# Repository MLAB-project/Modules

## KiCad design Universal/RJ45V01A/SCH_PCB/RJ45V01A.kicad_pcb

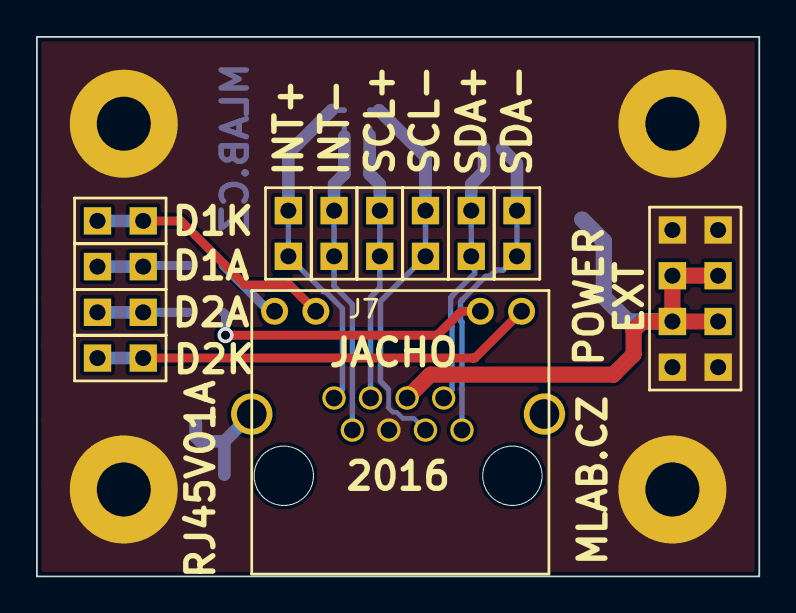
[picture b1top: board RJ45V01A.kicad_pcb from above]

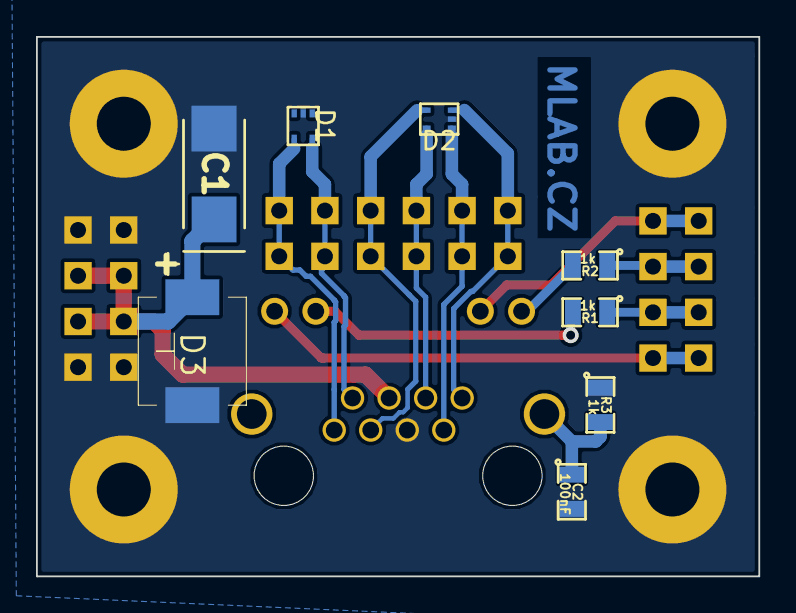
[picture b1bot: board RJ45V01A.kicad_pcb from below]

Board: 2 copper layers, 40.1 x 30.0 mm, 24 parts (8 on the bottom side), 15 nets.

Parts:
C1: 47uF; TantalC_SizeC_Reflow
C2: 100nF; SMD-0805
D1, D2: SP1001-04XTG; SOT-553
D3: SM15T18A; Diode-SMC_Standard
J1: JUMP_4X2; Straight_2x04
J3: JUMP_2x1; Straight_1x02
J4, J5, J6, J8, J9, J10, J11, J12, J13: JUMP_2x1; Straight_2x01
J7: RJ45_RJHSE-5384; RJHSE-5384(RJ45)
M1, M2, M3, M4: HOLE; MountingHole_3mm
R1, R2, R3: 1k; SMD-0805

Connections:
/D1_A: J6.1, J6.2, R2.1
/D1_K: J3.1, J3.2, J7.11
/D2_A: J5.1, J5.2, R1.1
/D2_K: J4.1, J4.2, J7.9
/INT+: D2.3, J7.8, J8.1, J8.2
/INT-: D2.1, J7.7, J9.1, J9.2
/SCL+: D2.5, J7.6, J10.1, J10.2
/SCL-: D2.4, J7.3, J11.1, J11.2
/SDA+: D1.5, J7.2, J12.1, J12.2
/SDA-: D1.4, J7.1, J13.1, J13.2
GND: C1.2, C2.2, D1.2, D2.2, D3.1, J1.1, J1.2, J1.7, J1.8, J7.5, M1.1, M2.1, M3.1, M4.1, R3.1
unnamed: C2.1, J7.13, R3.2
unnamed: J7.10, R1.2
unnamed: J7.12, R2.2
VCC: C1.1, D3.2, J1.3, J1.4, J1.5, J1.6, J7.4

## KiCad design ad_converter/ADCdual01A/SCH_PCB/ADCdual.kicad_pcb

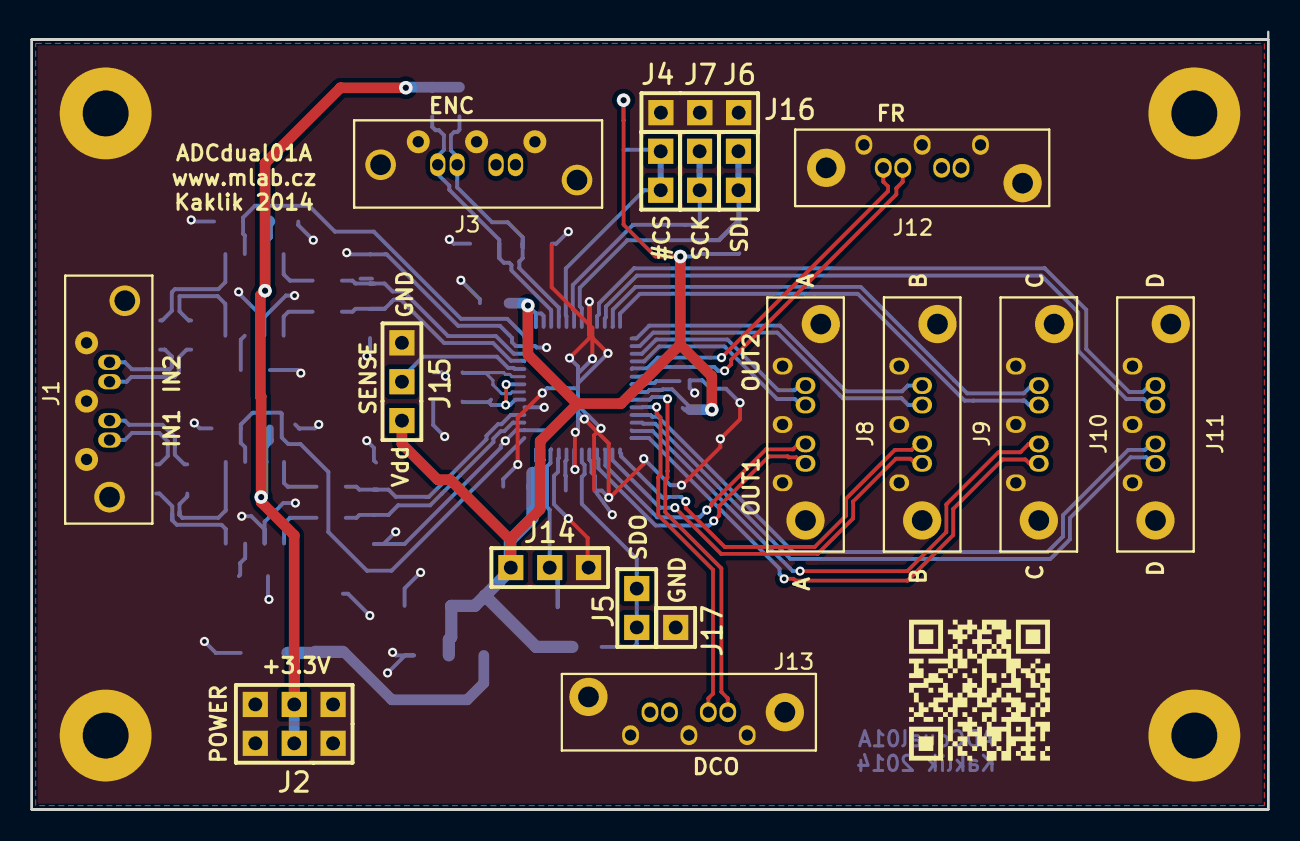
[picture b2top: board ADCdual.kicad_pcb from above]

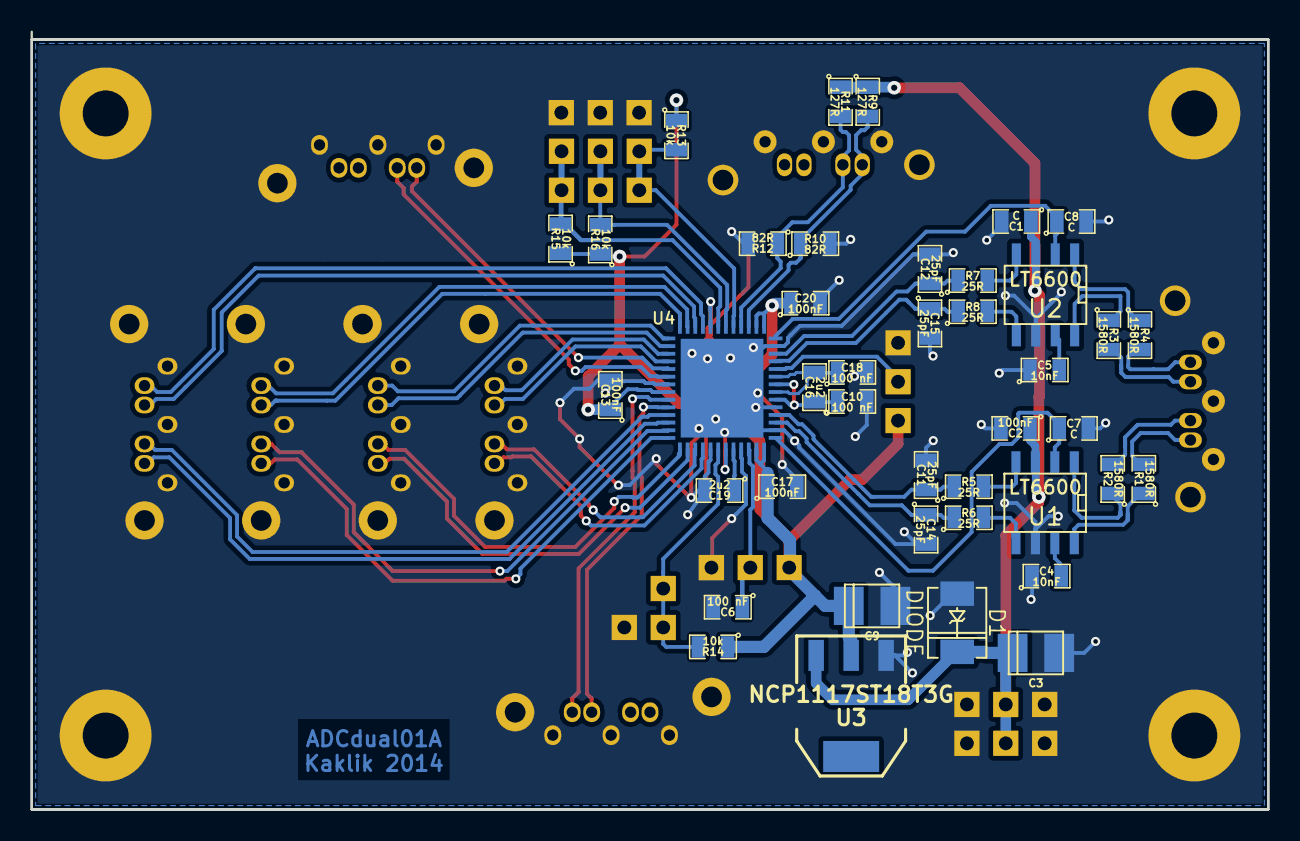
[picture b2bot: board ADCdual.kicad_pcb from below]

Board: 2 copper layers, 80.8 x 50.8 mm, 62 parts (41 on the bottom side), 54 nets.

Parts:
C1, C7, C8: C; SM0805
C2, C13, C17, C20: 100nF; SM0805
C3, C9: 10uF; c_tant_B
C4, C5: 10nF; SM0805
C6, C10, C18: 100 nF; SM0805
C11, C12, C14, C15: 25pF; SM0805
C16, C19: 2u2; SM0805
D1: DIODE; DO-214AC(SMA)
J1, J3: SATA7-67491-1030; SATA-7_THT_VERT
J2: JUMP_3X2_CONN; Pin_Header_Straight_2x03
J4, J5, J6, J7: JUMP_2_CONN; Pin_Header_Straight_2x01
J8, J9, J10, J11, J12, J13: SATA7-67491-1030; SATA-7_THT_VERT_2
J14: SENSE; Pin_Header_Straight_1x03
J15: PAR/SER; Pin_Header_Straight_1x03
J16: CONN_3; Pin_Header_Straight_1x03
J17: CONN_1; Pin_Header_Straight_1x01
P1, P2, P3, P4: CONN_1; MountingHole_3mm
R1, R2, R3, R4: 1580R; SM0805
R5, R6, R7, R8: 25R; SM0805
R9, R11: 127R; SM0805
R10, R12: 82R; SM0805
R13, R14, R15, R16: 10k; SM0805
U1, U2: LT6600; SO8E
U3: NCP1117ST18T3G; SOT223
U4: LTC2271; QFN52+1EP_HandSoldering

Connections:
3V3: C1.1, C2.1, C3.1, D1.2, J2.2, J2.5, R9.1, R11.1, U1.3, U2.3, U3.3
+1.8V: C9.1, C13.1, C17.1, C20.1, J14.1, J15.1, R13.1, R14.1, R15.1, R16.1, U3.2, U4.15, U4.16, U4.34, U4.51, U4.52
DGND: C1.2, C2.2, C3.2, C4.1, C5.1, C6.2, C7.2, C8.2, C9.2, C10.2, C11.2, C12.2, C13.2, C14.2, C15.2, C17.2, C18.2, C19.2, C20.2, D1.1, J1.1, J1.4, J1.7, J1.8, J1.9, J2.1, J2.3, J2.4, J2.6, J3.1, J3.4, J3.7, J3.8, J3.9, J8.1, J8.4, J8.7, J8.8, J8.9, J9.1, J9.4, J9.7, J9.8, J9.9, J10.1, J10.4, J10.7, J10.8, J10.9, J11.1, J11.4, J11.7, J11.8, J11.9, J12.1, J12.4, J12.7, J12.8, J12.9, J13.1, J13.4, J13.7, J13.8, J13.9, J14.3, J15.3, J16.1, J16.2, J16.3, J17.1, P1.1, P2.1, P3.1, P4.1, R10.2, R12.2, U1.6, U2.6, U3.1, U4.2, U4.5, U4.13, U4.22, U4.33, U4.45, U4.47, U4.49, U4.53
unnamed: C4.2, U1.7
unnamed: C5.2, U2.7
unnamed: C6.1, J14.2, U4.50
unnamed: C7.1, U1.2, U4.1
unnamed: C8.1, U2.2, U4.14
unnamed: C10.1, C16.1, U4.6, U4.8
unnamed: C11.1, R5.1, U4.4
unnamed: C12.1, R7.1, U4.12
unnamed: C14.1, R6.1, U4.3
unnamed: C15.1, R8.1, U4.11
unnamed: C16.2, C18.1, U4.7, U4.9
unnamed: C19.1, U4.48
unnamed: J1.2, R1.2
unnamed: J1.3, R2.2
unnamed: J1.5, R3.2
unnamed: J1.6, R4.2
unnamed: J3.2, R9.2, R10.1, U4.17
unnamed: J3.3, R11.2, R12.1, U4.18
unnamed: J4.1, J4.2, R13.2, U4.19
unnamed: J5.1, J5.2, R14.2, U4.46
unnamed: J6.1, J6.2, R15.2, U4.21
unnamed: J7.1, J7.2, R16.2, U4.20
unnamed: J8.2, U4.44
unnamed: J8.3, U4.43
unnamed: J8.5, U4.30
unnamed: J8.6, U4.29
unnamed: J9.2, U4.42
unnamed: J9.3, U4.41
unnamed: J9.5, U4.28
unnamed: J9.6, U4.27
unnamed: J10.2, U4.40
unnamed: J10.3, U4.39
unnamed: J10.5, U4.26
unnamed: J10.6, U4.25
unnamed: J11.2, U4.38
unnamed: J11.3, U4.37
unnamed: J11.5, U4.24
unnamed: J11.6, U4.23
unnamed: J12.2, U4.31
unnamed: J12.3, U4.32
unnamed: J13.2, U4.35
unnamed: J13.3, U4.36
unnamed: J15.2, U4.10
unnamed: R1.1, U1.8
unnamed: R2.1, U1.1
unnamed: R3.1, U2.8
unnamed: R4.1, U2.1
unnamed: R5.2, U1.4
unnamed: R6.2, U1.5
unnamed: R7.2, U2.4
unnamed: R8.2, U2.5

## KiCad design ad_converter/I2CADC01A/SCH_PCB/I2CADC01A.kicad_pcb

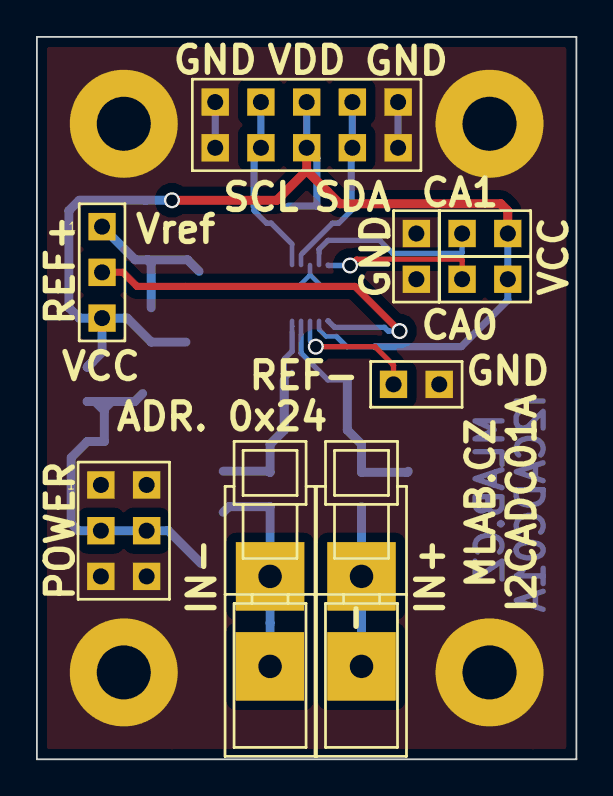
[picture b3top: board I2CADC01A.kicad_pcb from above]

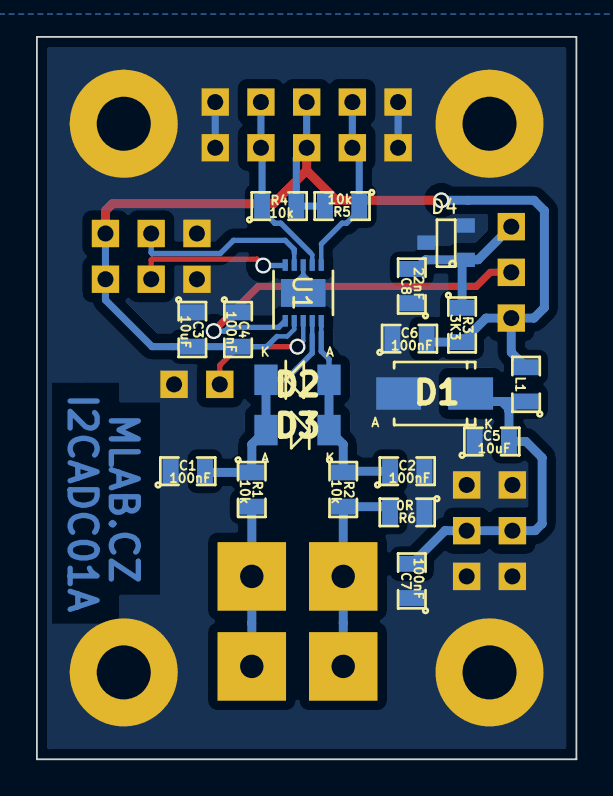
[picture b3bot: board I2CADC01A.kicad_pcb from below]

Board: 2 copper layers, 30.0 x 40.1 mm, 33 parts (20 on the bottom side), 14 nets.

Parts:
C1, C2, C4, C6, C7: 100nF; SMD-0805
C3, C5: 10uF; SMD-0805
C8: 22nF; SMD-0805
D1: M4; SMA_Standard
D2, D3: BAT46; MiniMELF_Standard
D4: LM4041-adj; SOT-23
J1: JUMP_3X2; Straight_2x03
J3, J8: CONN_2; Straight_2x01
J4: CONN_3; Straight_1x03
J5, J6: JUMP2_2x1; Straight_2x01
J7: JUMP_5X2; Straight_2x05
L1: BLM21PG300SN1D; SMD-0805
M1, M2, M3, M4: HOLE; MountingHole_3mm
P1, P2: _; WAGO256
R1, R2, R4, R5: 10k; SMD-0805
R3: 3K3; SMD-0805
R6: 0R; SMD-0805
U1: LTC2485; DFN-10-1EP_3x3mm_Pitch0.5mm

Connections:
/CA0: J5.2, U1.10
/CA1: J6.2, U1.9
/SCL: J7.7, J7.8, R5.1, U1.6
/SDA: J7.3, J7.4, R4.1, U1.7
GND: C1.1, C2.2, C3.1, C4.1, C5.1, C6.1, C7.1, C8.1, D1.1, D4.2, D4.3, J1.1, J1.2, J1.5, J1.6, J3.1, J7.1, J7.2, J7.9, J7.10, J8.1, J8.2, M1.1, M2.1, M3.1, M4.1, R6.1, U1.8, U1.11
unnamed: C1.2, D2.1, D3.2, R1.1, U1.4
unnamed: C2.1, D2.2, D3.1, R2.1, U1.5
unnamed: C5.2, C7.2, D1.2, J1.3, J1.4, L1.1
unnamed: C8.2, D4.1, J4.1, R3.1
unnamed: J3.2, U1.3
unnamed: J4.2, U1.1
unnamed: P1.1, R1.2
unnamed: P2.1, R2.2, R6.2
VCC: C3.2, C4.2, C6.2, J4.3, J5.1, J6.1, J7.5, J7.6, L1.2, R3.2, R4.2, R5.2, U1.2

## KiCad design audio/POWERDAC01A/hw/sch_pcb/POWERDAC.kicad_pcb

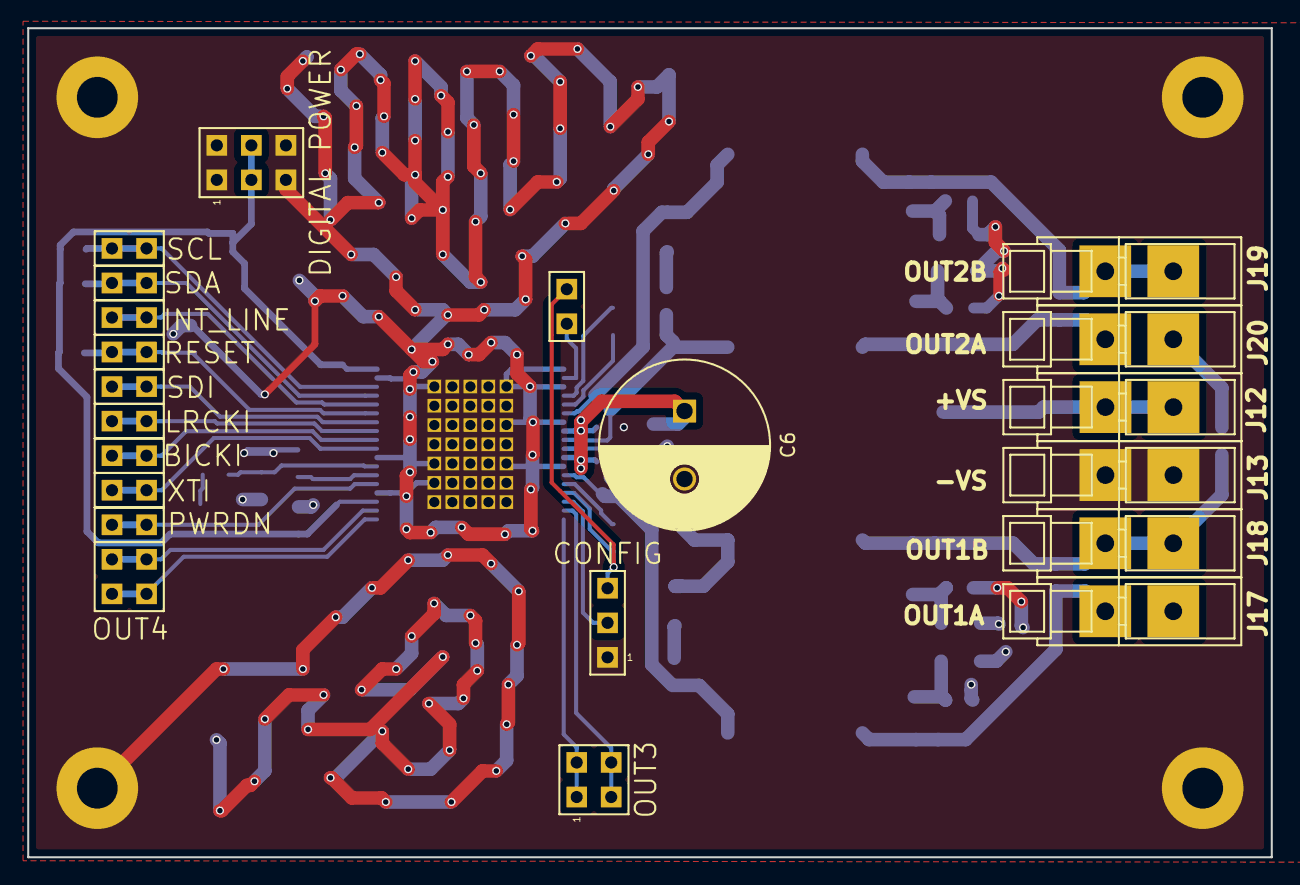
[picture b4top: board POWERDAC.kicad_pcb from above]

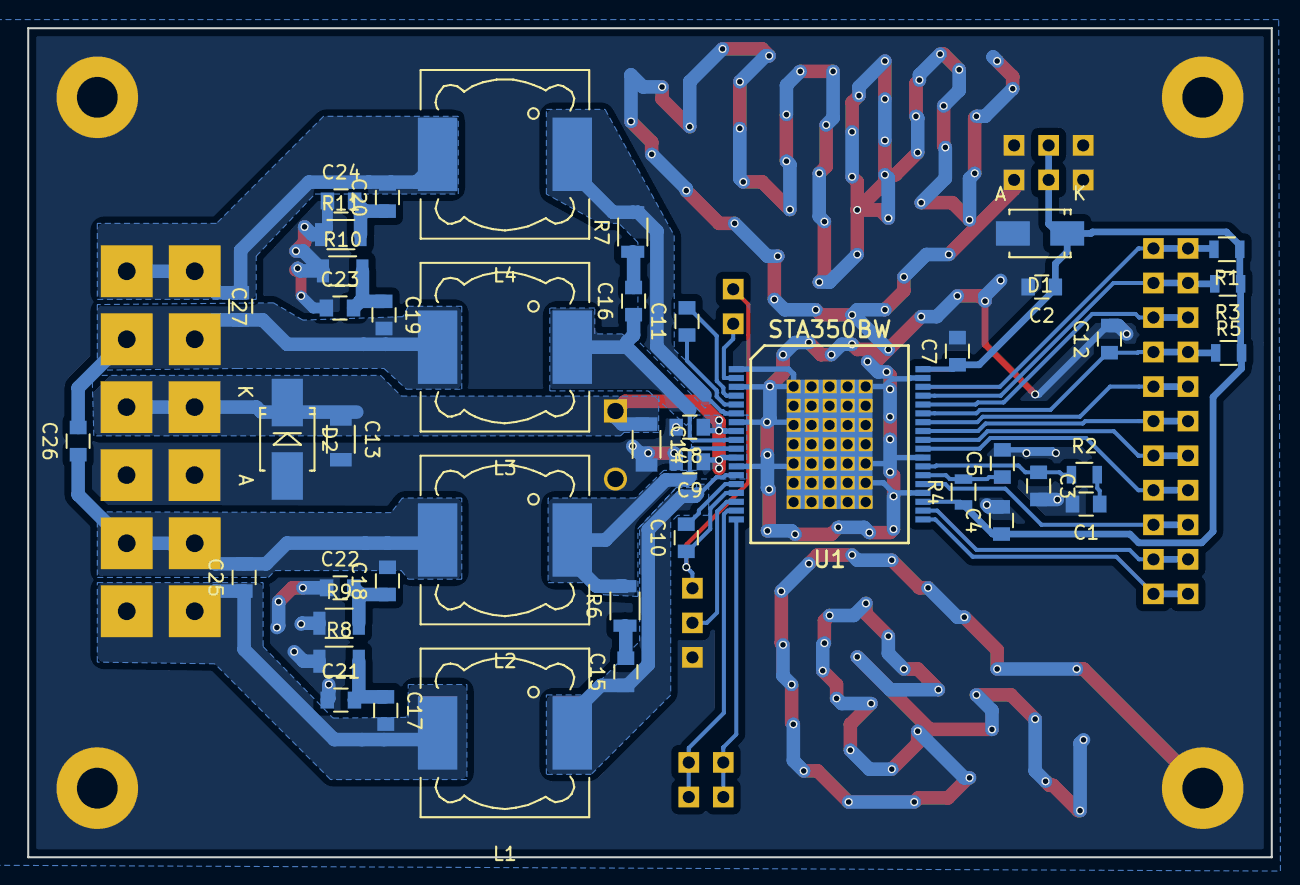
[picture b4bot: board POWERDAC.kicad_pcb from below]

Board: 2 copper layers, 91.4 x 61.0 mm, 69 parts (44 on the bottom side), 39 nets.

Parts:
C1: 4n7; C_0805
C2: 22uF/6.3V; C_0805
C3: 680p; C_0805
C4, C5, C7, C8, C9, C10, C11, C17, C18, C19, C20, C21, C22, C23, C24: 100nF; C_0805
C6: 1000uF/35V; C_Radial_D12.5_L25_P5
C12: 1nF; C_0805
C13, C14: 1uF/35V; C_1206
C15, C16: 330p; C_0805
C25, C27: 680nF; C_0805
C26: 1uF; C_0805
D1: M4; SMA_Standard
D2: M4; SMB_Handsoldering
J1: CONFIG; Straight_1x03
J2: DIGITAL POWER; Straight_2x03
J3: PWRDN; Straight_1x02
J4: INT_LINE; Straight_1x02
J5: SDA; Straight_1x02
J6: SCL; Straight_1x02
J7: SDI; Straight_1x02
J8: LRCKI; Straight_1x02
J9: XTI; Straight_1x02
J10: BICKI; Straight_1x02
J11: SA; Straight_1x02
J12: +VS; TerminalBlock_WAGO_256_RM5mm_1pol
J13: -VS; TerminalBlock_WAGO_256_RM5mm_1pol
J14: RESET; Straight_1x02
J15: OUT3; Straight_2x02
J16: OUT4; Straight_2x02
J17: OUT1A; TerminalBlock_WAGO_256_RM5mm_1pol
J18: OUT1B; TerminalBlock_WAGO_256_RM5mm_1pol
J19: OUT2B; TerminalBlock_WAGO_256_RM5mm_1pol
J20: OUT2A; TerminalBlock_WAGO_256_RM5mm_1pol
L1, L2, L3, L4: 15uH; Choke_SMD_12x12mm_h6mm
M1, M2, M3, M4: HOLE; MountingHole_3mm
R1, R3, R5: 10k; R_0805
R2: 2k2; R_0805
R4: 2R2; R_0805
R6, R7: 20; R_1206
R8, R9, R10, R11: 4R7; R_1206
U1: STA350BW; PowerSSO-36

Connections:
+3V3: C2.1, C4.1, C7.1, D1.1, J2.3, J2.4, R1.1, R3.1, R4.1, R5.1, U1.21, U1.36
GND: C1.2, C2.2, C3.2, C4.2, C5.2, C6.2, C7.2, C8.2, C9.2, C12.2, C13.2, C14.2, C21.1, C22.1, C23.1, C24.1, D1.2, D2.2, J1.1, J2.1, J2.2, J2.5, J2.6, J13.1, M1.1, M2.1, M3.1, M4.1, R8.1, R9.1, R10.1, R11.1, U1.1, U1.3, U1.7, U1.12, U1.22, U1.26, U1.35, U1.37
unnamed: C1.1, R2.2
unnamed: C3.1, R2.1, U1.25
unnamed: C5.1, R4.2, U1.24
unnamed: C10.2, U1.14
unnamed: C11.1, U1.5
unnamed: C11.2, U1.4
unnamed: C12.1, J14.1, J14.2, R5.2, U1.31
unnamed: C15.1, L1.1, U1.13
unnamed: C15.2, R6.1
unnamed: C16.1, L3.1, U1.9
unnamed: C16.2, R7.1
unnamed: C17.1, C21.2, R8.2
unnamed: C17.2, C25.1, J17.1, L1.2
unnamed: C18.1, C22.2, R9.2
unnamed: C18.2, C25.2, C26.1, J18.1, L2.2
unnamed: C19.1, C23.2, R10.2
unnamed: C19.2, C26.2, C27.1, J20.1, L3.2
unnamed: C20.1, C24.2, R11.2
unnamed: C20.2, C27.2, J19.1, L4.2
unnamed: J1.2, U1.16
unnamed: J3.1, J3.2, U1.23
unnamed: J4.1, J4.2, U1.32
unnamed: J5.1, J5.2, R3.2, U1.33
unnamed: J6.1, J6.2, R1.2, U1.34
unnamed: J7.1, J7.2, U1.30
unnamed: J8.1, J8.2, U1.29
unnamed: J9.1, J9.2, U1.27
unnamed: J10.1, J10.2, U1.28
unnamed: J11.2, U1.2
unnamed: J15.1, J15.2, U1.18
unnamed: J15.3, J15.4, U1.17
unnamed: J16.1, J16.2, U1.20
unnamed: J16.3, J16.4, U1.19
unnamed: L2.1, R6.2, U1.10
unnamed: L4.1, R7.2, U1.6
VCC: C6.1, C8.1, C9.1, C13.1, C14.1, D2.1, J12.1, U1.8, U1.11
VDD: C10.1, J1.3, J11.1, U1.15

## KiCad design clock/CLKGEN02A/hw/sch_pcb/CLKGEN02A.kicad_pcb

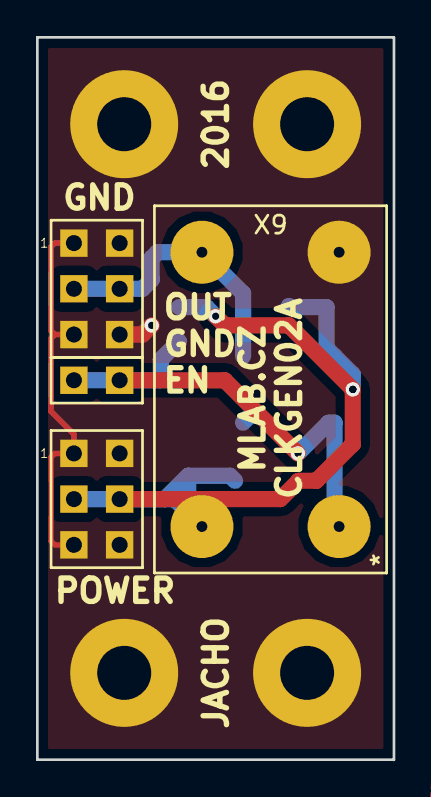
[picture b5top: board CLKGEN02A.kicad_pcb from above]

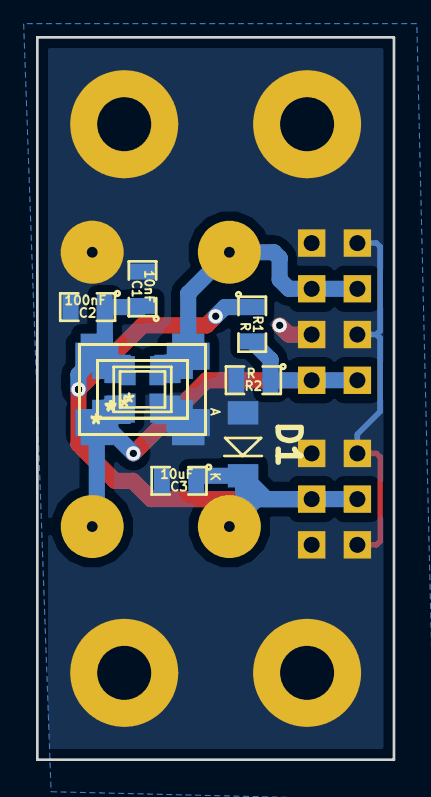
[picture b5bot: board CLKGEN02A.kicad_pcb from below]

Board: 2 copper layers, 19.8 x 40.1 mm, 21 parts (13 on the bottom side), 4 nets.

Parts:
C1: 10nF; SMD-0805
C2: 100nF; SMD-0805
C3: 10uF; SMD-0805
D1: BZV55C; Diode-MiniMELF_Standard
J1, J3: JUMP_3X2; Straight_2x03
J2: JUMP_2x1; Straight_1x02
M1, M2, M3, M4: HOLE; MountingHole_3mm
R1, R2: R; SMD-0805
X1: ASFL1, ASFLK; ASFL1
X2: CFPS-72,CFPS-73; CFPS-72,73
X3: ISM92
X4: ISM97
X6: I533_I534_I733_I734_Series; I533_1534_1733_1734
X7: ISM81
X8: ISM95
X9: OSC-F

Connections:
/EN: J2.1, J2.2, R1.2, R2.1, X1.1, X2.1, X3.1, X4.1, X6.1, X7.1, X8.1, X9.1
/OUT: J3.3, J3.4, X1.3, X2.3, X3.3, X4.3, X6.3, X7.3, X8.3, X9.3
GND: C1.2, C2.2, C3.2, D1.2, J1.1, J1.2, J1.5, J1.6, J3.1, J3.2, J3.5, J3.6, M1.1, M2.1, M3.1, M4.1, R2.2, X1.2, X2.2, X3.2, X4.2, X6.2, X7.2, X8.2, X9.2
VCC: C1.1, C2.1, C3.1, D1.1, J1.3, J1.4, R1.1, X1.4, X2.4, X3.4, X4.4, X6.4, X7.4, X8.4, X9.4

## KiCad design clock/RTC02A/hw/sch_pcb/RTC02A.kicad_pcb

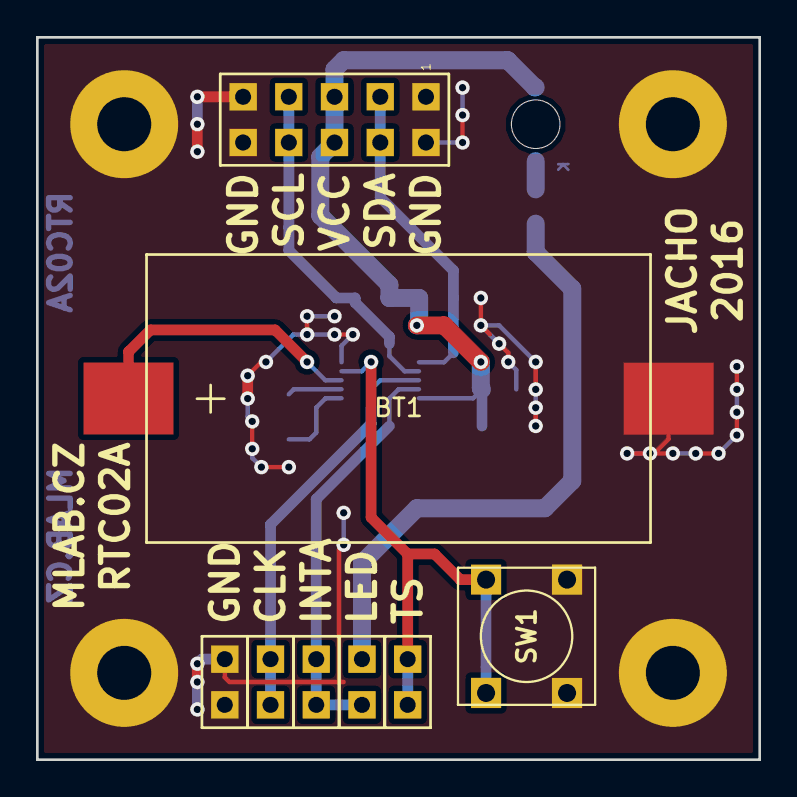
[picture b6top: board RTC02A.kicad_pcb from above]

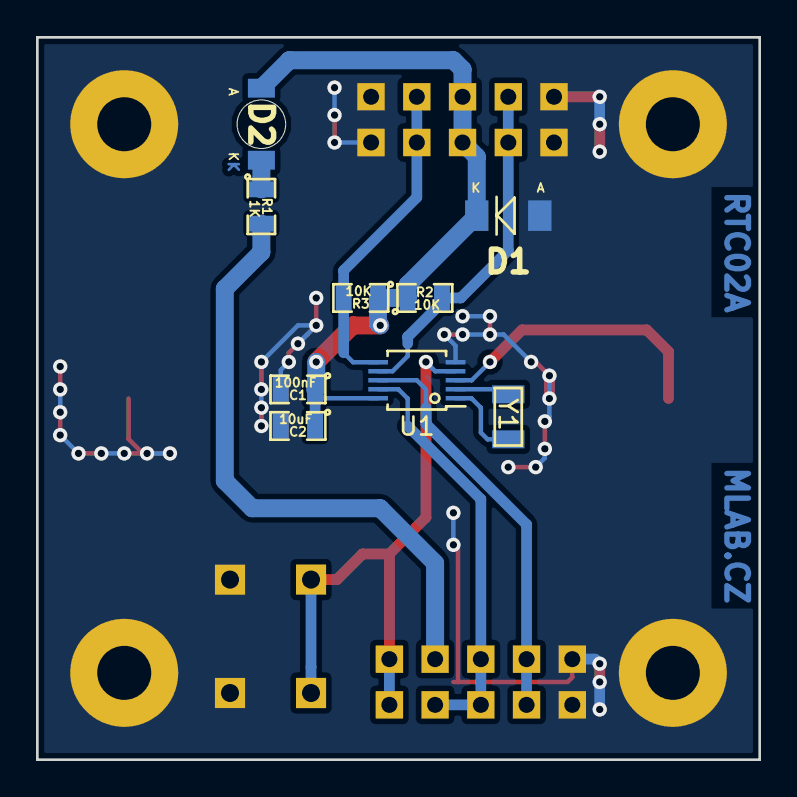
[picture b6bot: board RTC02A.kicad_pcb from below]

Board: 2 copper layers, 40.1 x 40.1 mm, 21 parts (9 on the bottom side), 12 nets.

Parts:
BT1: CH28-2032
C1: 100nF; SMD-0805
C2: 10uF; SMD-0805
D1: BZV55C; Diode-MiniMELF_Standard
D2: LED; LED_1206
J1: JUMP_5X2; Straight_2x05
J2: JUMP2_2x1; Straight_2x01
J3, J4, J5, J6: JUMP_2x1; Straight_2x01
M1, M2, M3, M4: HOLE; MountingHole_3mm
R1: 1K; SMD-0805
R2, R3: 10K; SMD-0805
SW1: SW_PUSH; SW_PUSH_SMALL
U1: PCF85263A; TSSOP-10_3x3mm_Pitch0.5mm
Y1: ABS07-120-32.768KHZ-T; ABS07

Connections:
/CLK: J4.1, J4.2, U1.8
/INTA: J2.1, J3.1, J3.2, U1.9
/SCL: J1.7, J1.8, R2.2, U1.7
/SDA: J1.3, J1.4, R3.2, U1.6
/TS: J5.1, J5.2, SW1.1, U1.4
GND: BT1.2, C1.2, C2.2, D1.2, J1.1, J1.2, J1.9, J1.10, J6.1, J6.2, M1.1, M2.1, M3.1, M4.1, SW1.2, U1.5
unnamed: BT1.1, U1.3
unnamed: D2.1, R1.1
unnamed: J2.2, R1.2
unnamed: U1.1, Y1.2
unnamed: U1.2, Y1.1
VCC: C1.1, C2.1, D1.1, D2.2, J1.5, J1.6, R2.1, R3.1, U1.10

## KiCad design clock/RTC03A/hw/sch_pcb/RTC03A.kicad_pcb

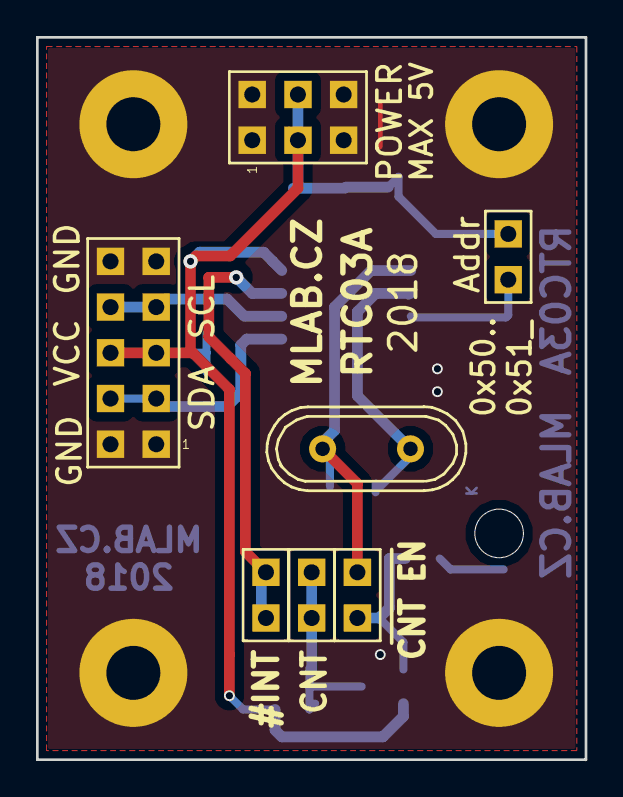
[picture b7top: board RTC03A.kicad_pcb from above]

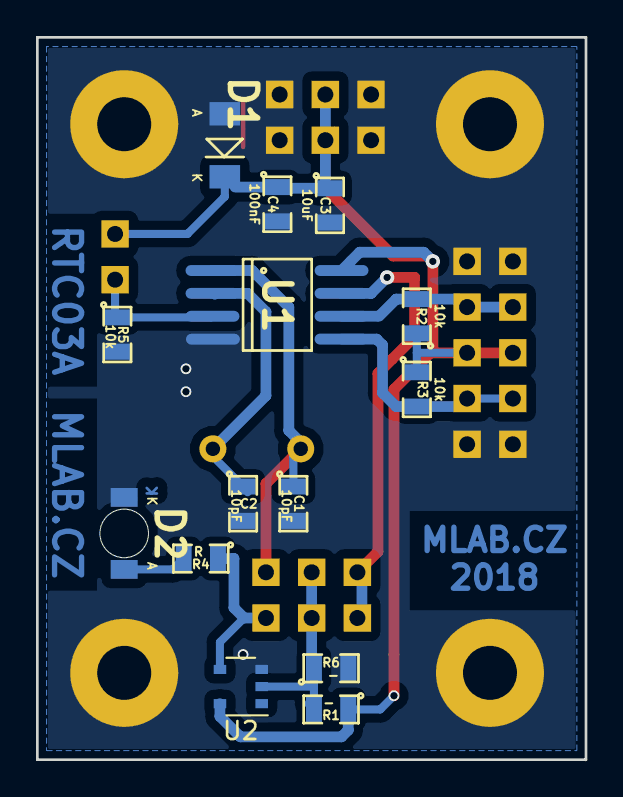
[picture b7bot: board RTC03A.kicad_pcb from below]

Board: 2 copper layers, 30.5 x 40.1 mm, 25 parts (14 on the bottom side), 11 nets.

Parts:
C1, C2: 10pF; SMD-0805
C3: 10uF; SMD-0805
C4: 100nF; SMD-0805
D1: ZENER-5.6V; Diode-MiniMELF_Standard
D2: LED; LED_1206
J2: CONN1_2; Straight_2x01
J3: JUMP_2x1; Straight_2x01
J4: JUMP_5X2; Straight_2x05
J5: JUMP_3X2; Straight_2x03
J6: JUMP2_2x1; Straight_2x01
J7: JUMP_2x1; Straight_1x02
M1, M2, M3, M4: HOLE; MountingHole_3mm
R1, R6: -; SMD-0805
R2, R3, R5: 10k; SMD-0805
R4: R; SMD-0805
U1: PCF8583; SO-8
U2: 74AHC1G14GV; TSOP-5_1.65x3.05mm_P0.95mm
Y1: Crystal; Crystal_HC49-U_Vertical

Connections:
/COUNT: J7.1, J7.2, R1.2, R6.1, U2.2
GND: C1.2, C2.2, C3.2, C4.2, D1.2, D2.1, J4.1, J4.2, J4.9, J4.10, J5.1, J5.2, J5.5, J5.6, M1.1, M2.1, M3.1, M4.1, R5.2, R6.2, U1.4, U2.3
unnamed: C1.1, J6.1, U1.1, Y1.2
unnamed: C2.1, U1.2, Y1.1
unnamed: D2.2, R4.2
unnamed: J2.1, R5.1, U1.3
unnamed: J3.1, J3.2, U1.7
unnamed: J4.3, J4.4, R3.2, U1.5
unnamed: J4.7, J4.8, R2.2, U1.6
unnamed: J6.2, R4.1, U2.4
VCC: C3.1, C4.1, D1.1, J2.2, J4.5, J4.6, J5.3, J5.4, R1.1, R2.1, R3.1, U1.8, U2.5

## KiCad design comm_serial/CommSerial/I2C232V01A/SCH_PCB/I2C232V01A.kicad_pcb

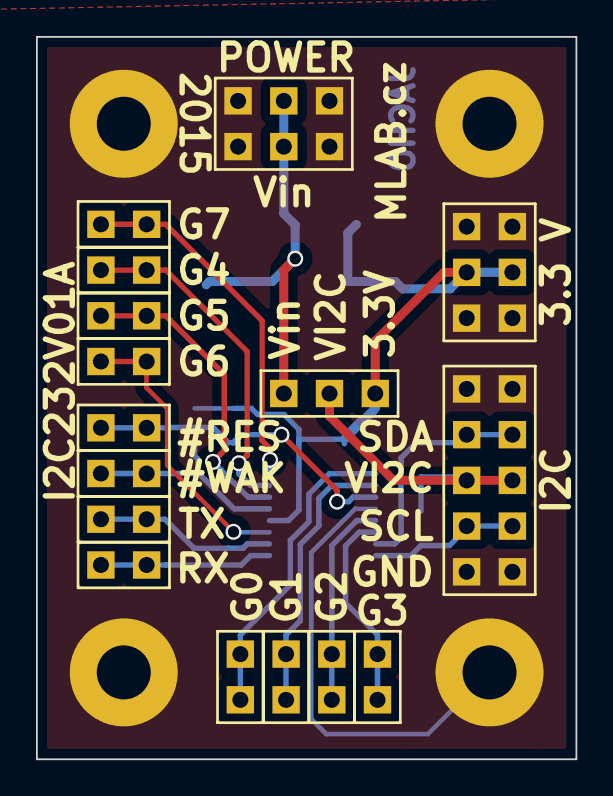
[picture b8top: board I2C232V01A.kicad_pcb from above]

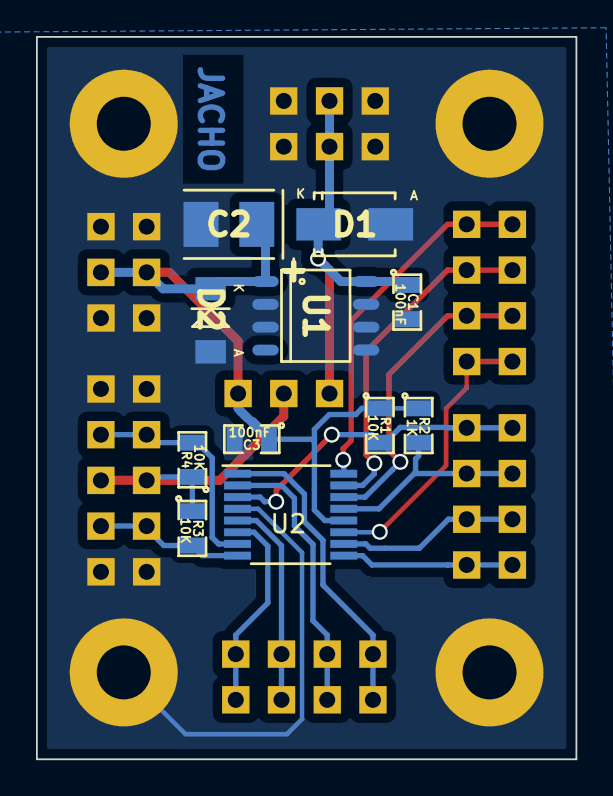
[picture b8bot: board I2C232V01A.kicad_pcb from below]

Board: 2 copper layers, 30.0 x 40.1 mm, 31 parts (11 on the bottom side), 18 nets.

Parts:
C1, C3: 100nF; SMD-0805
C2: 10uF; TantalC_SizeB_Reflow
D1: M4; SMA_Standard
D2: BZV55C-3,6V; MiniMELF_Standard
J1, J6: JUMP_3X2; Straight_2x03
J2, J3, J4, J5, J7, J8, J9, J10, J11, J12, J13, J14: JUMP_2x1; Straight_2x01
J15: CONN_3; Straight_1x03
J16: JUMP_5X2; Straight_2x05
P1, P2, P3, P4: sroub; MountingHole_3mm
R1, R3, R4: 10K; SMD-0805
R2: 1K; SMD-0805
U1: LE33CD; SO-8
U2: SC18IM700; TSSOP-16_4.4x5mm_Pitch0.65mm

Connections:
+3V3: C2.1, C3.1, D2.2, J6.3, J6.4, J15.1, R1.1, R2.1, U1.1, U2.12
/#RES: J4.1, J4.2, R1.2, U2.3
/#WAK: J5.1, J5.2, R2.2, U2.13
/G0: J7.1, J7.2, U2.1
/G1: J8.1, J8.2, U2.2
/G2: J9.1, J9.2, U2.5
/G3: J10.1, J10.2, U2.6
/G4: J11.1, J11.2, U2.15
/G5: J12.1, J12.2, U2.14
/G6: J13.1, J13.2, U2.11
/G7: J14.1, J14.2, U2.16
/RX: J3.1, J3.2, U2.9
/SCL: J16.7, J16.8, R3.2, U2.8
/SDA: J16.3, J16.4, R4.2, U2.7
/TX: J2.1, J2.2, U2.10
GND: C1.2, C2.2, C3.2, D1.1, D2.1, J1.1, J1.2, J1.5, J1.6, J6.1, J6.2, J6.5, J6.6, J16.1, J16.2, J16.9, J16.10, P1.1, P2.1, P3.1, P4.1, U1.2, U1.3, U1.5, U1.6, U1.7, U2.4
unnamed: J15.2, J16.5, J16.6, R3.1, R4.1
VCC: C1.1, D1.2, J1.3, J1.4, J15.3, U1.8
